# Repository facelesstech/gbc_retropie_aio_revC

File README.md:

# gbc_retropie_aio_revC
gbc_retropie_aio_revC

GBC Retropie AIO Blog post - https://facelesstech.wordpress.com/2022/02/11/gbc-retropie-aio-rev-c/ 
GBC Retropie AIO build guide - https://facelesstech.wordpress.com/2021/09/19/gbc-retropie-aio-rev-c-build-guide/

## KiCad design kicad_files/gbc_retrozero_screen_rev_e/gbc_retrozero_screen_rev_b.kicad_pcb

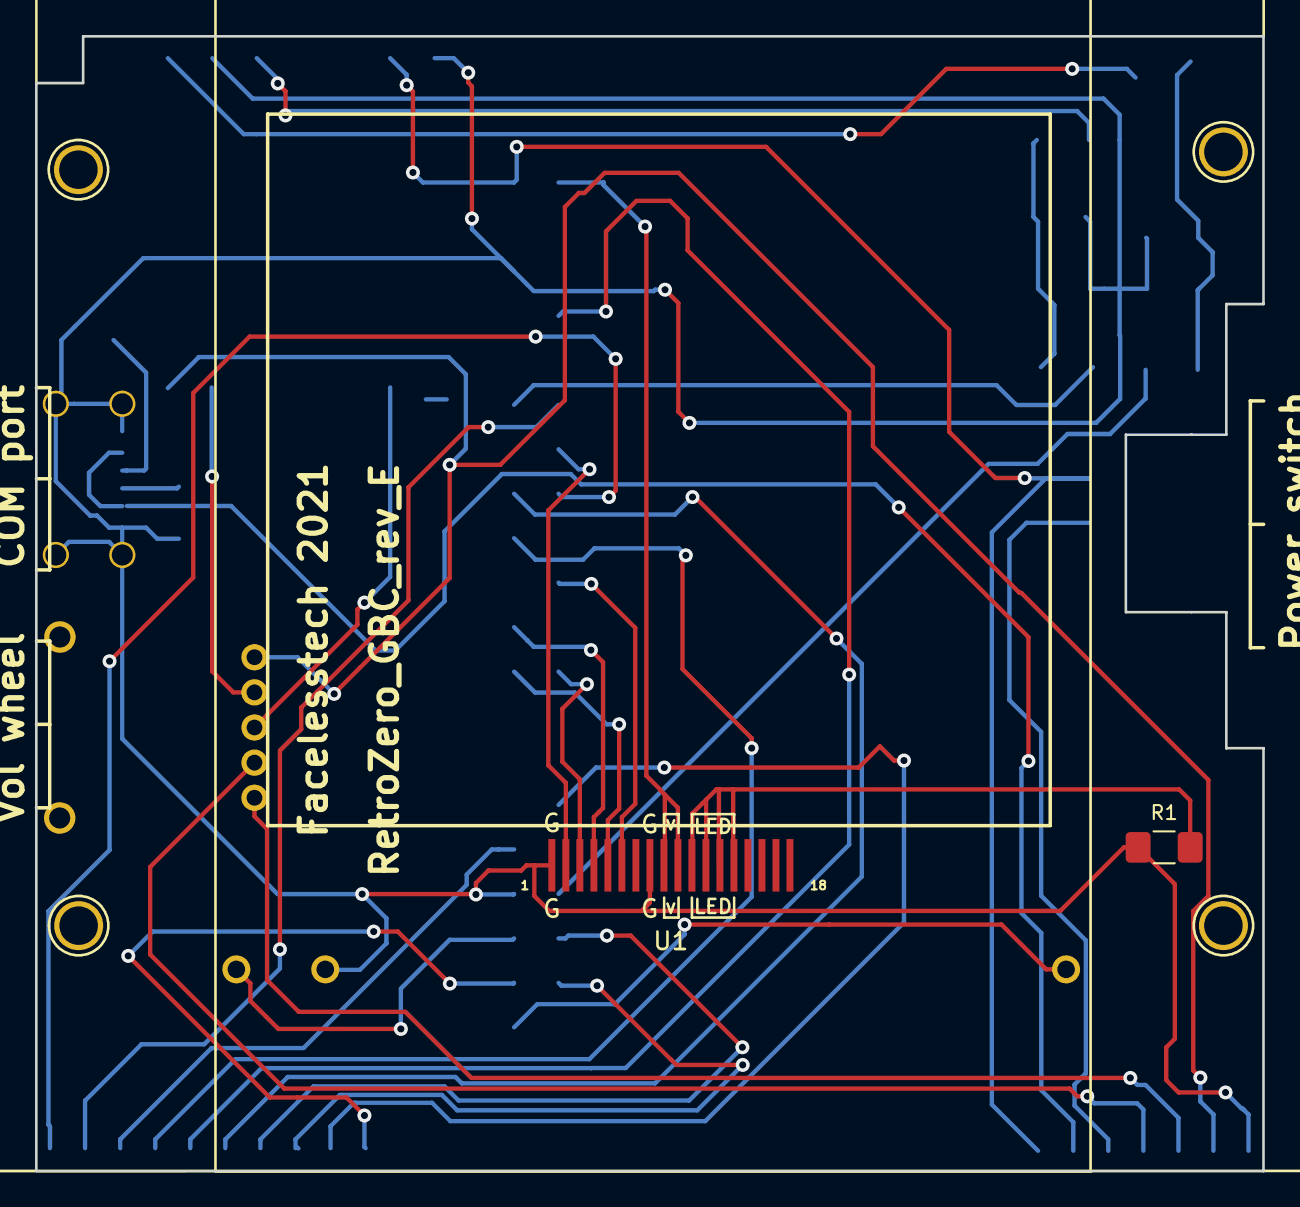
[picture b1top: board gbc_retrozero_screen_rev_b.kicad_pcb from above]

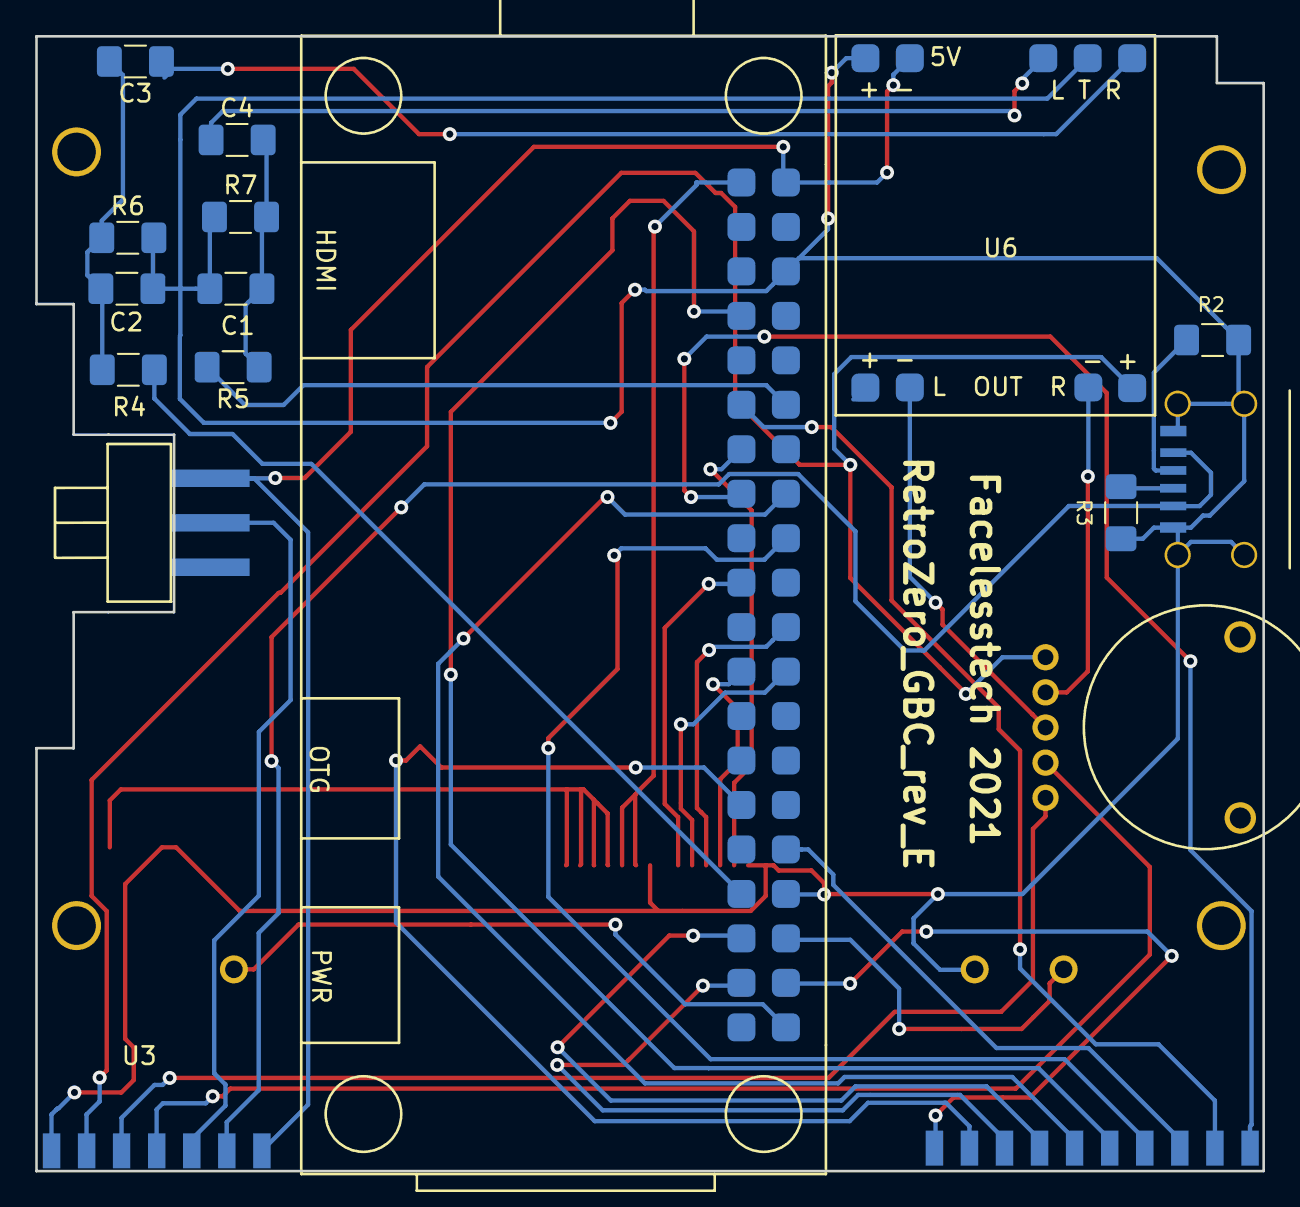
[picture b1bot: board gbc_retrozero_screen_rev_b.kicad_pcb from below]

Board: 2 copper layers, 70.1 x 64.8 mm, 21 parts (17 on the bottom side), 36 nets.

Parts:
C1, C2: C33nf; C_1206_3216Metric_Pad1.42x1.75mm_HandSolder
C3, C4: C10uf; C_1206_3216Metric_Pad1.42x1.75mm_HandSolder
J1: Raspberry_Pi_2_3; raspberry_pi_gpio_SMD_outline_under_holes
R1, R2, R3: R; R_1206_3216Metric_Pad1.42x1.75mm_HandSolder
R4, R5: R270; R_1206_3216Metric_Pad1.42x1.75mm_HandSolder
R6, R7: R150; R_1206_3216Metric_Pad1.42x1.75mm_HandSolder
SW1: SW_Push_SPDT; 3_pin_switch_smd_side_mount
U1: 2.4_screen_ribbon; 2.8_screen_ribbon_breakout
U2: gbc_just_button_connector; GBC_button_headers_only_slim
U3: gbc_power_connector; GBC_power_and_sound_slim
U4: sound_pot_5pin; GBC_pot_custom
U5: gbc_l_and_r_3pin; GBC_L_and_R_3pin
U6: pam8403; PAM8403_custom_smd
U7: usb_c_6pin; USB_C_6PIN_custom
U8: gbc_l_and_r_1pin; GBC_L_and_R_1pin

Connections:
unnamed: C1.1, C2.2, J1.6, J1.34, R1.1, R2.1, R3.1, R6.2, R7.1, U1.1, U1.8, U3.1, U5.1, U6.2, U6.5, U7.1
unnamed: C1.2, C4.2, R5.1, R7.2
unnamed: C2.1, C3.2, R4.1, R6.1
unnamed: C3.1, U6.1
unnamed: C4.1, U6.3
unnamed: J1.1, U1.9, U1.10
unnamed: J1.2, SW1.3, U3.7, U6.4
unnamed: J1.7, U2.6
unnamed: J1.11, U2.9
unnamed: J1.12, R5.2
unnamed: J1.13, U1.2
unnamed: J1.15, U2.10
unnamed: J1.16, U2.5
unnamed: J1.18, U2.7
unnamed: J1.19, U1.6
unnamed: J1.22, U1.4
unnamed: J1.23, U1.3
unnamed: J1.24, U1.5
unnamed: J1.29, U2.2
unnamed: J1.32, U2.8
unnamed: J1.33, R4.2
unnamed: J1.35, U2.4
unnamed: J1.36, U5.3
unnamed: J1.37, U2.3
unnamed: J1.38, U2.1
unnamed: J1.40, U8.3
unnamed: R1.2, U1.11, U1.12, U1.13, U1.14
unnamed: R2.2, U7.3
unnamed: R3.2, U7.4
unnamed: SW1.2, U3.5
unnamed: U3.2, U4.1, U6.6
unnamed: U3.3, U4.5
unnamed: U3.4, U4.4
unnamed: U3.6, U7.2
unnamed: U4.2, U6.7
unnamed: U4.3, U6.8

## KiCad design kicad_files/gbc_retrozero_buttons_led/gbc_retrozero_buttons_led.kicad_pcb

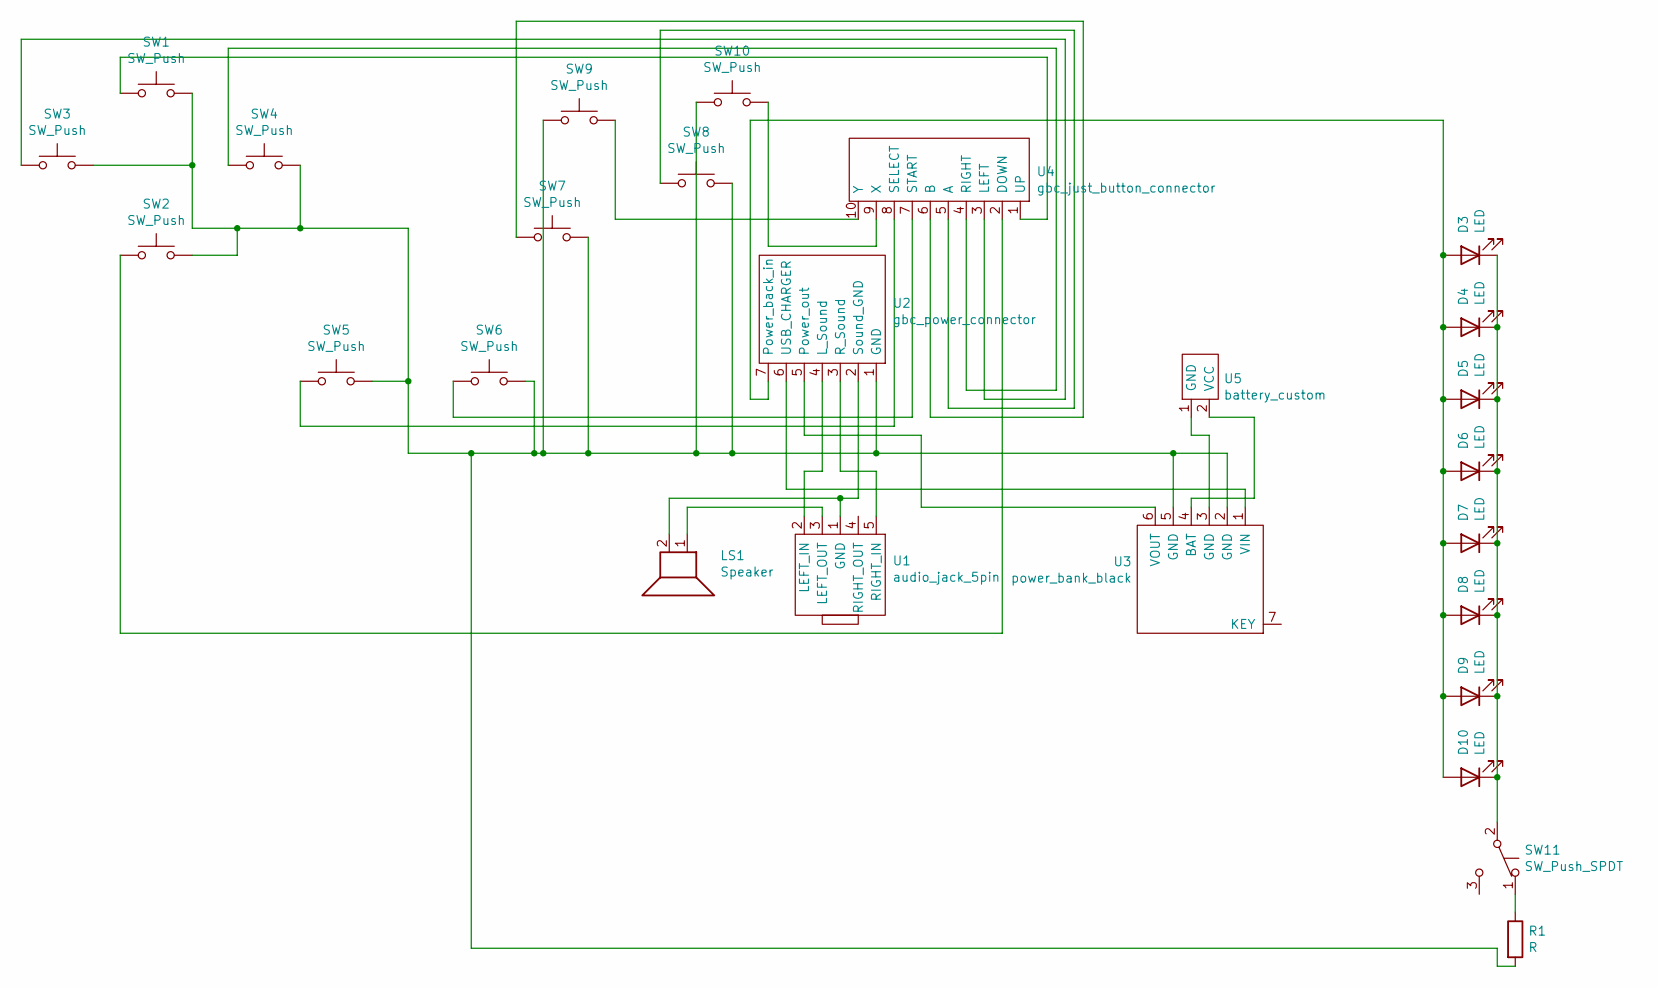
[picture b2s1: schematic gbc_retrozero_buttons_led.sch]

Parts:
D3, D4, D5, D6, D7, D8, D9, D10: LED; LED_0603_1608Metric_Pad1.05x0.95mm_HandSolder
LS1: Speaker; speaker_2pin
R1: R; R_1206_3216Metric_Pad1.30x1.75mm_HandSolder
SW1, SW2, SW3, SW4, SW5, SW6: SW_Push; gbc_pad_buttons_small
SW7, SW8: SW_Push; gbc_start_button_custom
SW9: SW_Push; button_soft_touch_drill_hole_custom
SW10: SW_Push; button_soft_touch_2_hole_custom
SW11: SW_Push_SPDT; tiny_smd_slide_switch_adjustable
U1: audio_jack_5pin; 5_pin_3.5_jack
U2: gbc_power_connector; GBC_power_and_sound_slim
U3: power_bank_black; power_bank_black_smd
U4: gbc_just_button_connector; GBC_button_headers_only_slim
U5: battery_custom; vcc_gnd_2pin_custom

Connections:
unnamed: D3.1 (K), D4.1 (K), D5.1 (K), D6.1 (K), D7.1 (K), D8.1 (K), D9.1 (K), D10.1 (K), SW11.2 (B)
unnamed: D3.2 (A), D4.2 (A), D5.2 (A), D6.2 (A), D7.2 (A), D8.2 (A), D9.2 (A), D10.2 (A), U2.7 (Power_back_in)
unnamed: LS1.1, U1.3 (LEFT_OUT)
unnamed: LS1.2, U1.1 (GND), U2.2 (Sound_GND)
unnamed: R1.1, SW11.1 (A)
unnamed: R1.2, SW1.2, SW2.2, SW3.2, SW4.2, SW5.2, SW6.2, SW7.2, SW8.2, SW9.1, SW10.1, U2.1 (GND), U3.2 (GND), U3.5 (GND)
unnamed: SW1.1, U4.1 (UP)
unnamed: SW2.1, U4.2 (DOWN)
unnamed: SW3.1, U4.3 (LEFT)
unnamed: SW4.1, U4.4 (RIGHT)
unnamed: SW5.1, U4.8 (SELECT)
unnamed: SW6.1, U4.7 (START)
unnamed: SW7.1, U4.6 (B)
unnamed: SW8.1, U4.5 (A)
unnamed: SW9.2, U4.10 (Y)
unnamed: SW10.2, U4.9 (X)
unnamed: U1.2 (LEFT_IN), U2.4 (L_Sound)
unnamed: U1.5 (RIGHT_IN), U2.3 (R_Sound)
unnamed: U2.5 (Power_out), U3.6 (VOUT)
unnamed: U2.6 (USB_CHARGER), U3.1 (VIN)
unnamed: U3.3 (GND), U5.1 (GND)
unnamed: U3.4 (BAT), U5.2 (VCC)

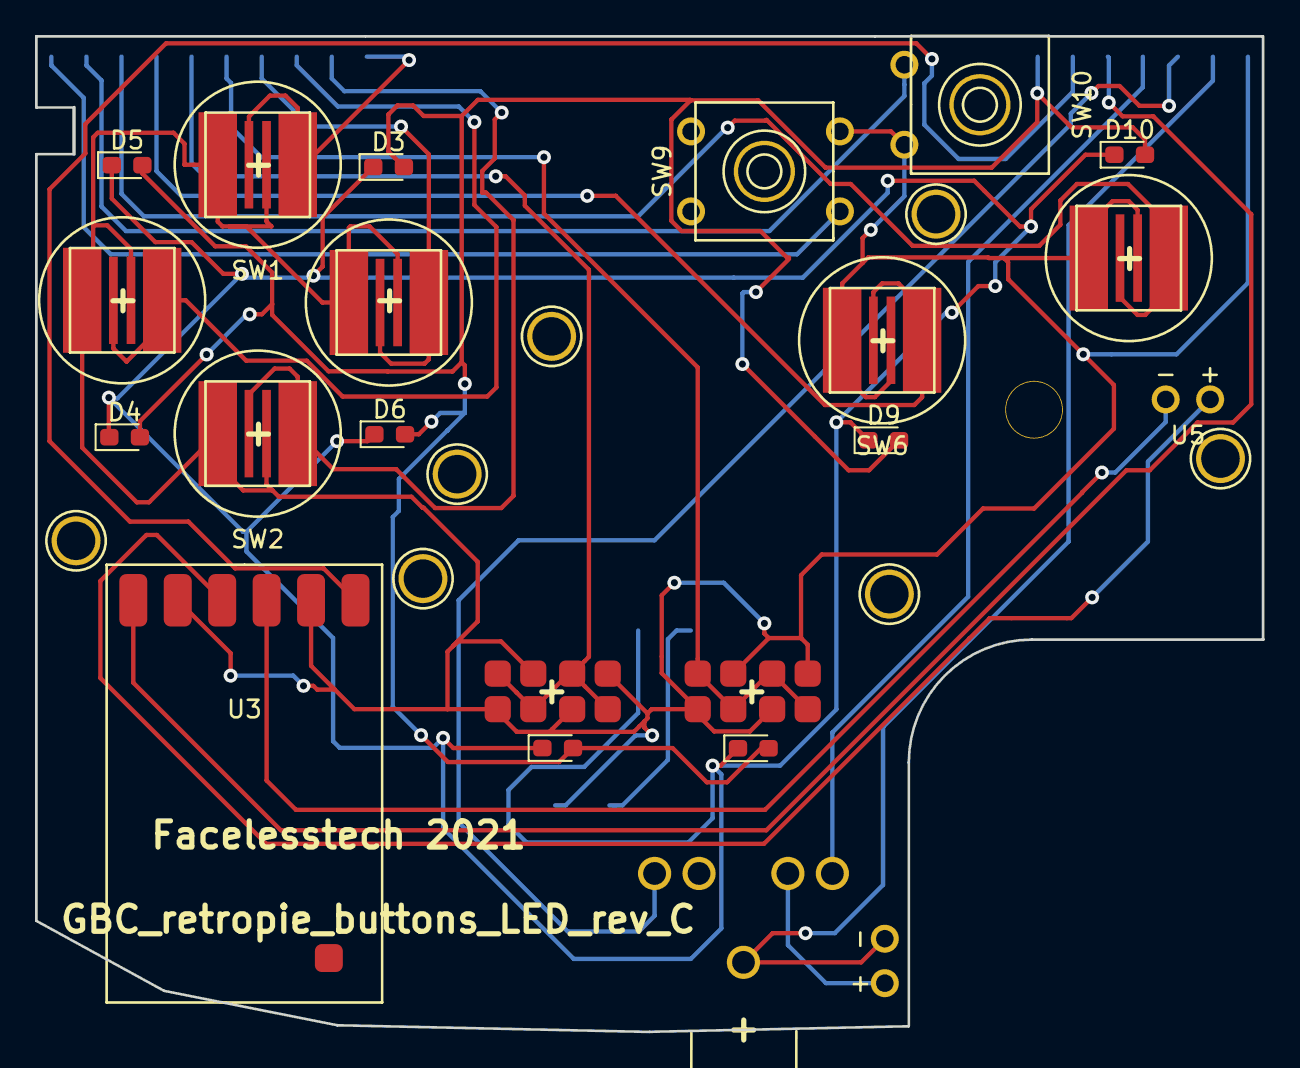
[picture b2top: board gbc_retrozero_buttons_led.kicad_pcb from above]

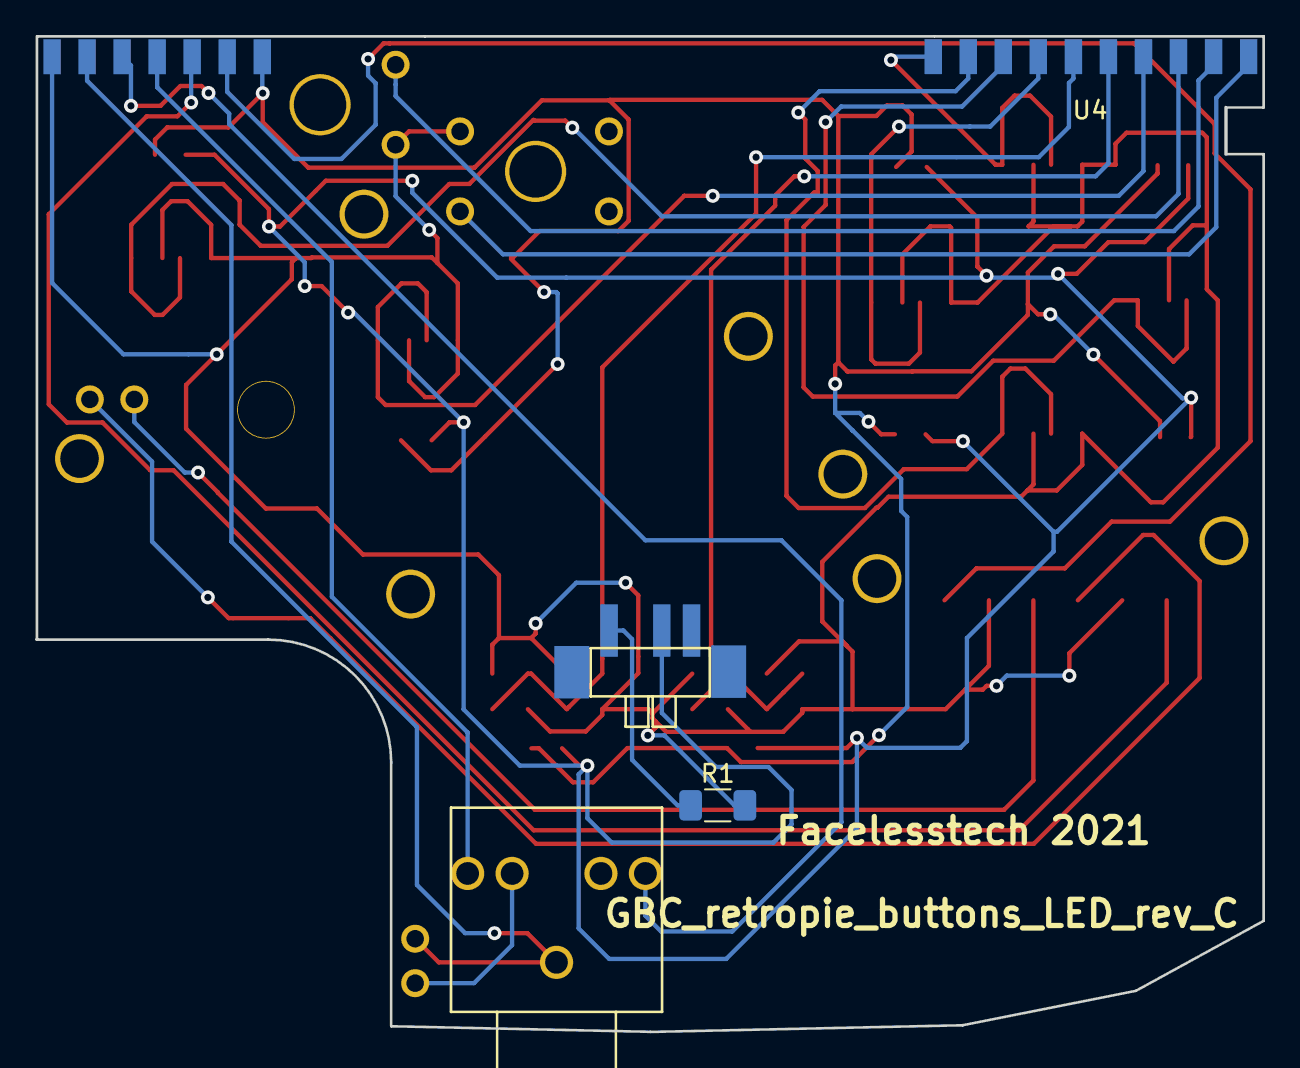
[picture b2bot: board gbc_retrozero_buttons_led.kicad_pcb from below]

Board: 2 copper layers, 70.1 x 56.9 mm, 26 parts (5 on the bottom side), 22 nets.

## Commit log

2022-01-15 PCB files
2022-01-15 all the 3d print files
2022-01-15 removed folder
2022-01-15 added stl files
2022-02-14 fixed issus with J1-PAD36 and trace
2022-03-07 added blog post links
2023-05-27 changed the folder name to reflect the board rev name
